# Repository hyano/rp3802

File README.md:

# RP3802: Tiny YM3802 emulator by Raspberry Pi Pico

RP3802 is a pin-level emulator of the YAMAHA MIDI control chip YM3802 using a Raspberry Pi Pico.

## Notes

* Please use at your own risk.
* The input/output voltage of the Raspberry Pi Pico's GPIO is 3.3V, while the input/output voltage of the YM3802 is 5V. However, no level shifter is used for cost reduction.
* The Raspberry Pi Pico is overclocked to 250MHz for operation.
* Serial I/F settings are fixed at 31,250bps, 8bits, no parity.
* Supports only major functions for X68000 games and utilities.

## Pin assignment

| Pico          | Direction | Description       | Comment       |
| ------------- | --------- | ----------------- | ------------- |
| GPIO 0        | Output    | YM3802 TxD        | UART TX       |
| GPIO 1        | Input     | YM3802 RxD        | UART RX       |
| GPIO 2-4      | Input     | YM3802 A0-A2      |               |
| GPIO 5-12     | Input     | YM3802 D0-D7      |               |
| GPIO 13       | Input     | /CS \| /RD        | <-- GPIO 20   |
| GPIO 14       | Input     | /CS \| /WR        | <-- GPIO 21   |
| GPIO 15       | Input     | YM3802 /IC        |               |
| GPIO 16       | Outut     | YM3802 /IRQ       |               |
| GPIO 17       | Input     | YM3802 /RD        |               |
| GPIO 18       | Input     | YM3802 /CS        |               |
| GPIO 19       | Input     | YM3802 /WR        |               |
| GPIO 20       | Output    | /CS \| /RD        | --> GPIO 13   |
| GPIO 21       | Output    | /CS \| /RD        | --> GPIO 14   |
| GPIO 22       | Output    | LED (HEARTBEAT)   |               |
| GPIO 26       | Output    | LED (TX)          |               |
| GPIO 27       | Output    | LED (RX)          |               |
| GPIO 28       | Output    | LED (IRQ)         |               |

## Implementation status

| internal block functions  | Status                |
| ------------------------  | --------------------- |
| Transmitter               | Implemented           |
| FIFO-Tx                   | Implemented           |
| Receiver                  | Implemented           |
| FIFO-Rx                   | Implemented           |
| Break detector            | Not implemented       |
| FIFO-ITx                  | Work in progress      |
| Idle detector             | Not implemented       |
| Off-line detector         | Not implemented       |
| MIDI clock filter         | Implemented           |
| Address hunter            | Not implemented       |
| SYNC detector             | Not implemented       |
| MIDI clock timer          | Implemented           |
| SYNC controller           | Not implemented       |
| CLICK counter             | Implemented           |
| MIDI clock interpolator   | Not implemented       |
| Recording counter         | Not implemented       |
| Playback counter          | Not implemented       |
| MIDI message detector     | Work in progress      |
| FIFO-IRx                  | Work in progress      |
| MIDI message distributor  | Work in progress      |
| General-purpose timer     | Implemented           |
| I/O controller            | Not implemented       |
| IRQ controller            | Implemented           |

## License

RP3802 is licensed under the MIT License. See [LICENSE](LICENSE).

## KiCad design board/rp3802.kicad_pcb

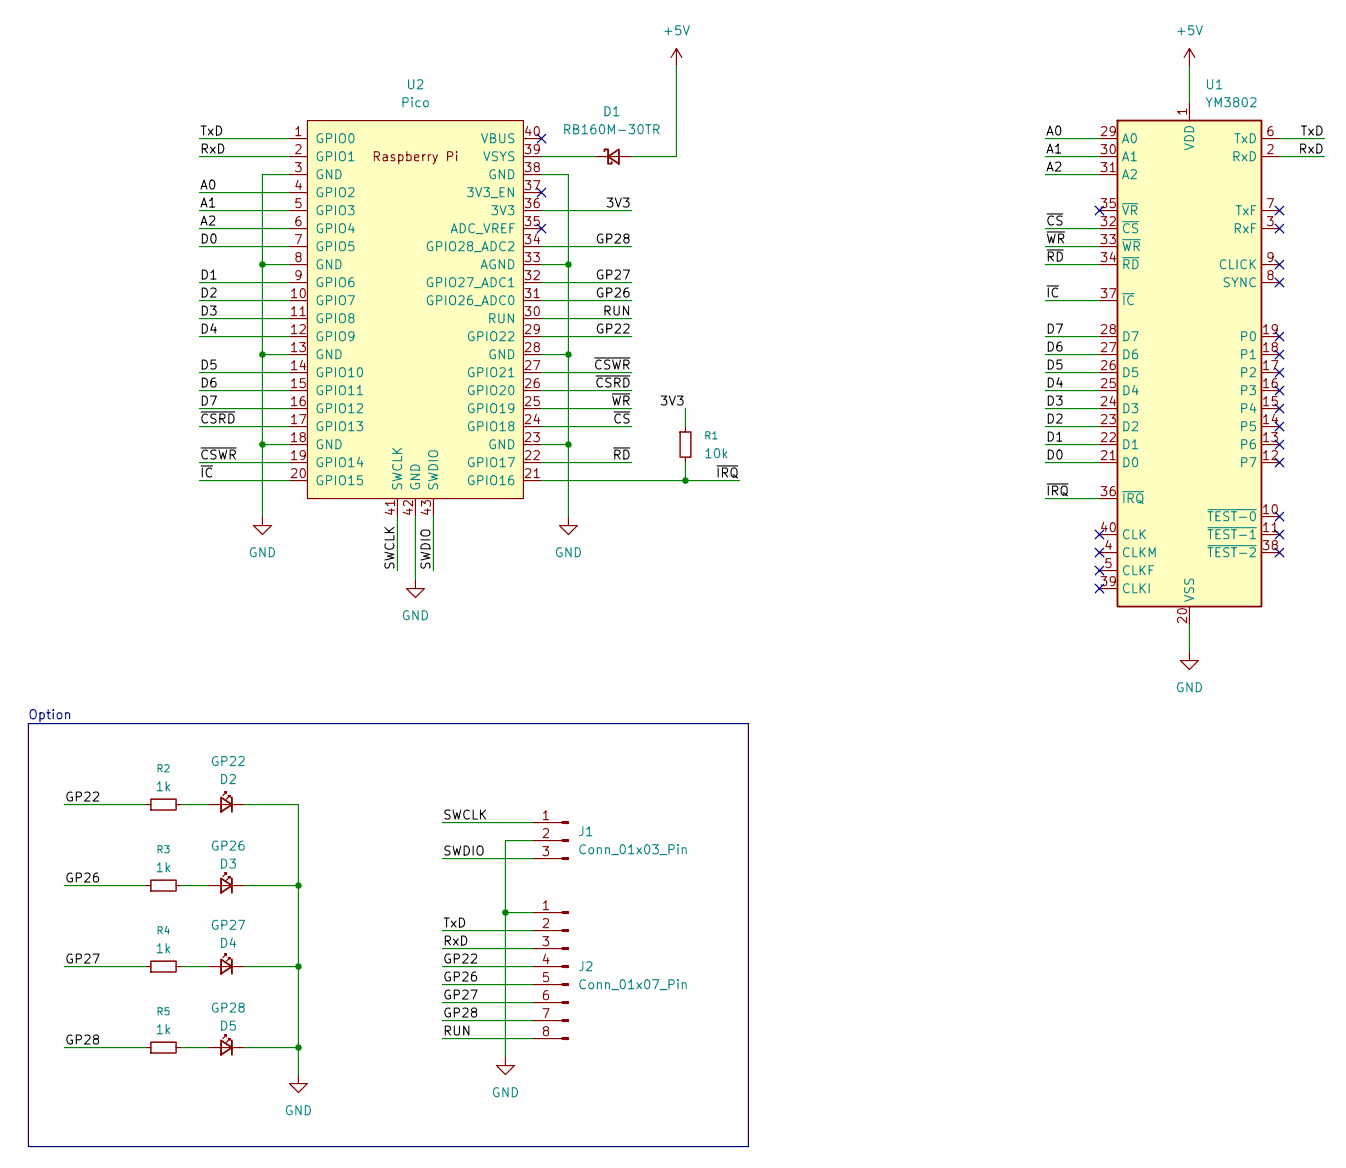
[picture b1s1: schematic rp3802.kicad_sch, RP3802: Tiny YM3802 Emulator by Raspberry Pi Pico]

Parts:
D1: RB160M-30TR; D_SOD-123
D2: GP22; LED_0603_1608Metric_Pad1.05x0.95mm_HandSolder
D3: GP26; LED_0603_1608Metric_Pad1.05x0.95mm_HandSolder
D4: GP27; LED_0603_1608Metric_Pad1.05x0.95mm_HandSolder
D5: GP28; LED_0603_1608Metric_Pad1.05x0.95mm_HandSolder
J1: Conn_01x03_Pin; PinHeader_1x03_P2.54mm_Horizontal
J2: Conn_01x07_Pin; PinHeader_1x08_P2.54mm_Horizontal
R1: 10k; R_0603_1608Metric_Pad0.98x0.95mm_HandSolder
R2, R3, R4, R5: 1k; R_0603_1608Metric_Pad0.98x0.95mm_HandSolder
U1: YM3802; DIP-40_W15.24mm_NO_IC
U2: Pico; RPi_Pico_SMD_TH

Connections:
+5V: D1.2 (A), U1.1 (VDD)
/3V3: R1.1, U2.36 (3V3)
/A0: U1.29 (A0), U2.4 (GPIO2)
/A1: U1.30 (A1), U2.5 (GPIO3)
/A2: U1.31 (A2), U2.6 (GPIO4)
/D0: U1.21 (D0), U2.7 (GPIO5)
/D1: U1.22 (D1), U2.9 (GPIO6)
/D2: U1.23 (D2), U2.10 (GPIO7)
/D3: U1.24 (D3), U2.11 (GPIO8)
/D4: U1.25 (D4), U2.12 (GPIO9)
/D5: U1.26 (D5), U2.14 (GPIO10)
/D6: U1.27 (D6), U2.15 (GPIO11)
/D7: U1.28 (D7), U2.16 (GPIO12)
/GP22: J2.4, R2.1, U2.29 (GPIO22)
/GP26: J2.5, R3.1, U2.31 (GPIO26_ADC0)
/GP27: J2.6, R4.1, U2.32 (GPIO27_ADC1)
/GP28: J2.7, R5.1, U2.34 (GPIO28_ADC2)
/RUN: J2.8, U2.30 (RUN)
/RxD: J2.3, U1.2 (RxD), U2.2 (GPIO1)
/SWCLK: J1.1, U2.41 (SWCLK)
/SWDIO: J1.3, U2.43 (SWDIO)
/TxD: J2.2, U1.6 (TxD), U2.1 (GPIO0)
/~CSRD: U2.17 (GPIO13), U2.26 (GPIO20)
/~CSWR: U2.19 (GPIO14), U2.27 (GPIO21)
/~CS: U1.32 (~CS), U2.24 (GPIO18)
/~IC: U1.37 (~IC), U2.20 (GPIO15)
/~IRQ: R1.2, U1.36 (~IRQ), U2.21 (GPIO16)
/~RD: U1.34 (~RD), U2.22 (GPIO17)
/~WR: U1.33 (~WR), U2.25 (GPIO19)
GND: D2.1 (K), D3.1 (K), D4.1 (K), D5.1 (K), J1.2, J2.1, U1.20 (VSS), U2.3 (GND), U2.8 (GND), U2.13 (GND), U2.18 (GND), U2.23 (GND), U2.28 (GND), U2.33 (AGND), U2.38 (GND), U2.42 (GND)
unnamed: D1.1 (K), U2.39 (VSYS)
unnamed: D2.2 (A), R2.2
unnamed: D3.2 (A), R3.2
unnamed: D4.2 (A), R4.2
unnamed: D5.2 (A), R5.2

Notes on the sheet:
Option

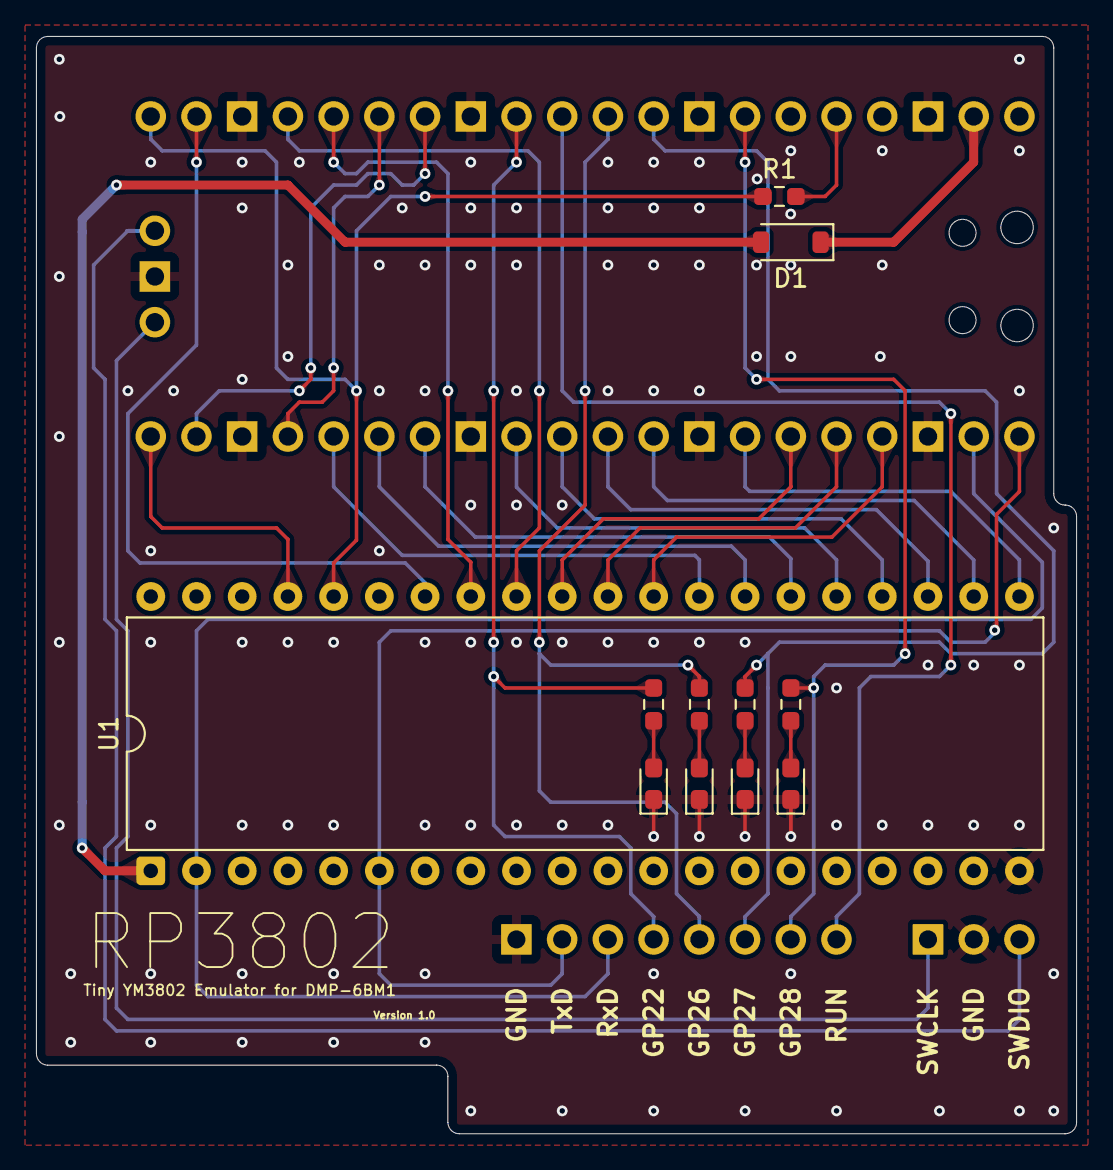
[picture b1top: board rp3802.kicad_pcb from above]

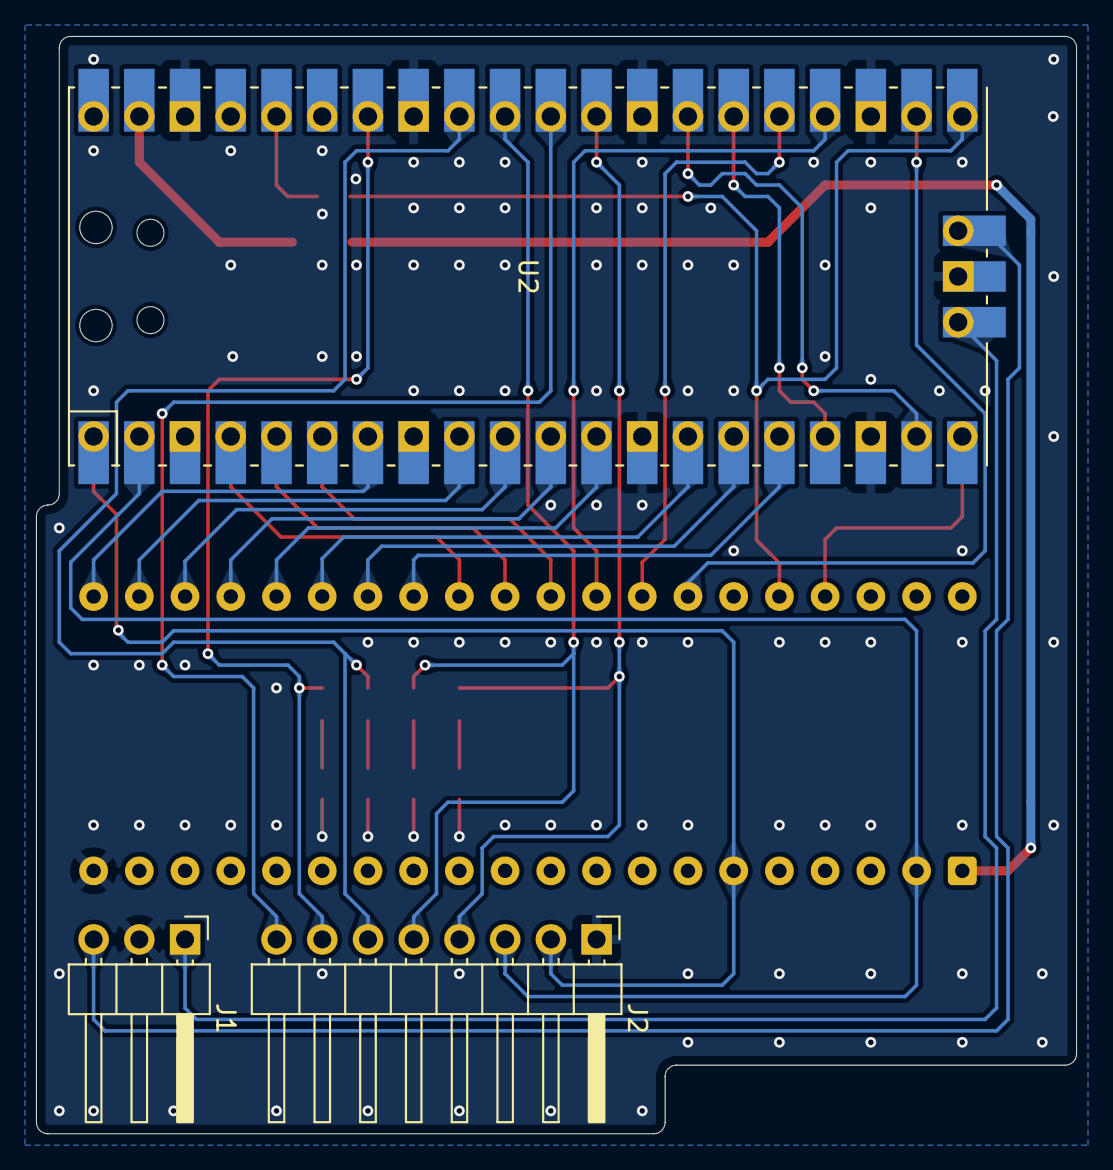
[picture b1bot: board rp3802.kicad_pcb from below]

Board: 2 copper layers, 57.8 x 61.0 mm, 14 parts (3 on the bottom side), 35 nets.

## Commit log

2025-05-06 added README.md
2025-05-06 fixed FIFO-Rx reading.
2025-05-06 added debug message for UART Tx/Rx.
2025-05-06 implement ICR.
2025-05-06 implement Initial clear by RGR.
2025-05-06 implement Initial clear by /IC pin
2025-05-06 fixed IC handling.
2025-05-06 changed read/write priority.
2025-05-06 fixed typo.
2025-05-06 re-changed read/write priority.
2025-05-10 fixed indent.
2025-05-10 activate GP timer only if count > 1.
2025-05-10 renamed fifo::peek to fifo::front.
2025-05-10 check UART TX availability on transmit.
2025-05-10 implement FIFO-TX/RX control.
2025-05-10 update TX_RX status with lock.
2025-05-10 Implement MIDI-clock timer, click counter.
2025-05-10 use ym3802_reg_value().
2025-05-10 add comment for Click Counter IRQ.
2025-05-10 no data on read.
2025-05-10 prepare for over clocking.
2025-05-11 initialize YM3802 in core0.
2025-05-11 fixed timer handling.
2025-05-11 added DEBUG_PRINTF().
2025-05-11 added heartbeat. fixed DEBUG_PRINTF().
2025-05-11 update bus access verbose message.
2025-05-11 debugging...
2025-05-11 for performance check.
2025-05-17 use Raspberry Pi Pico vscode extention.
2025-05-18 changed GPIO assignment.
2025-05-18 fixed UART baudrate.
2025-05-20 fixed usage of in instruction.
2025-05-20 optimize.
2025-05-20 fixed comment.
2025-05-24 debugging.
2025-05-25 change pin assign & use another pio to check CS/RD/WR & debugging.
2025-05-29 changed signal edge detection.
2025-05-30 fixed reset by RGR.
2025-05-30 add board/ to prevent wrong commit.
2025-05-30 add MIDI clock filter.
2025-05-30 update Rx status after clear FIFO-Rx.
2025-05-30 implement FIFO-Rx overflow.
2025-05-31 implement FIFO-IRx.
2025-05-31 extract MIDI clock message from FIFO-IRx.
2025-05-31 implement FIFO-ITx.
2025-05-31 fixed FIFO ITx.
2025-05-31 disabled debug logging.
2025-05-31 add current status.
2025-05-31 disable debug wait.
2025-05-31 build with GitHub Actions.
2025-05-31 tiny fix.
2025-06-01 add KiCad files.
2025-06-04 fixed typo in sheet titles.
2025-06-06 added LED control.
2025-06-06 updated README.
2025-06-06 fixed link for LICENSE.
2025-06-06 fixed description for pin assignment.
2025-06-06 shrink access buffer size.
2025-06-06 added static.
2025-06-06 added pico2 build.
2025-06-07 added Pico2 3D model.
2025-06-07 changed /IRQ pull up register value.
2025-06-07 change YM3802 footprint from DIP to PinHeader.
2025-06-08 use on-board LED as access buffer monitor.
2025-06-08 optimize access buffer profiling.
2025-06-15 upload artifact as a single file.
2025-06-15 archive from same directory.
2025-06-15 action for release.
2025-06-15 add write permission for release.
2025-07-05 update IRQ status when IER is updated.
2025-07-05 update IRQ status on reset.
2025-07-05 added identify RP3802 feature.
2025-07-05 send all note off message on reset.
2025-07-05 bump minor version.
2025-07-05 send initialize message via FIFO on core0.
2025-07-05 clean up UART TX.
